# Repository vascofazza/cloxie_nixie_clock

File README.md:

# Cloxie

Schematics and code for Cloxie: my Nixie Tube Clock.

The circuit and custom PCB are designed around the popular IN-14 Nixie tubes.

You can find the schematics here: https://github.com/vascofazza/cloxie_nixie_clock/blob/main/nixie_board/schematics.pdf

Watch the clock in action: https://www.youtube.com/watch?v=ZD35oEGX9IY

## Features

- NTP time sync over Wi-Fi
- The tubes are dimmable via PWM
- 6 RGB leds under the tubes with configurable patterns
- Automatic brightness control with a photoresistor
- Configurable via an onboard web server (reachable on the local network at: http://cloxie.local)
- Configurable via a dedicated Android App (available here: https://github.com/vascofazza/Cloxie-connect)
- Optional temperature sensor
- Alarm/Timer/StopWatch functionalities

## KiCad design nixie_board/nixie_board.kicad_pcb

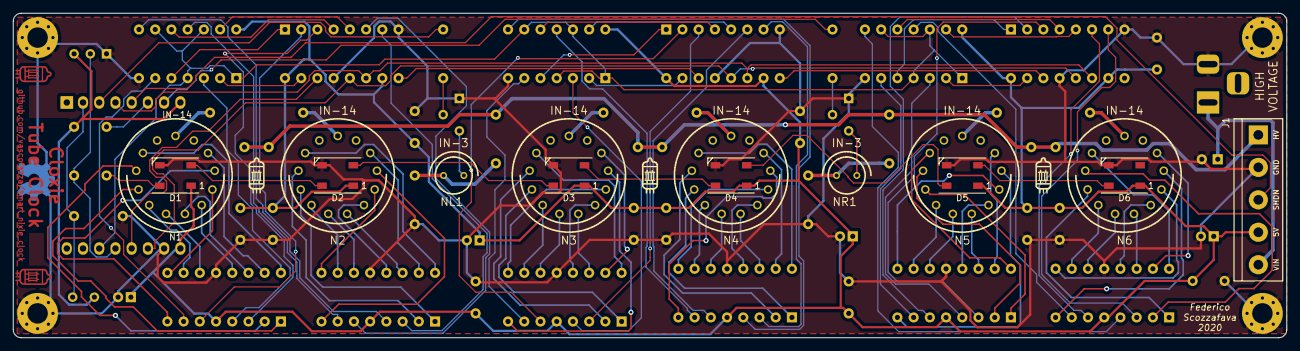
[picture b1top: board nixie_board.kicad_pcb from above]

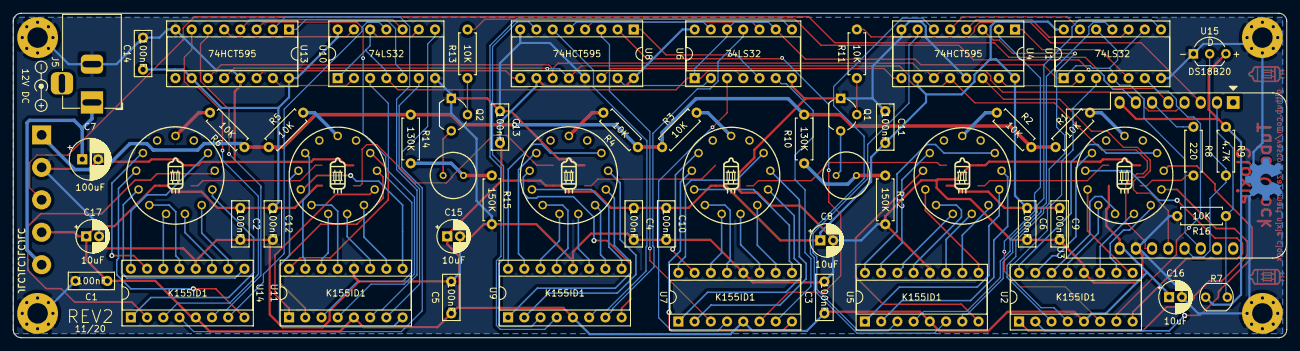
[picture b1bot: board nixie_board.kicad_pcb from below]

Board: 2 copper layers, 199.4 x 50.8 mm, 85 parts (59 on the bottom side), 131 nets.

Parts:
C1, C2, C3, C4, C5, C6, C9, C10, C11, C12, C13, C14: 100nF; C_Disc_D7.0mm_W2.5mm_P5.00mm
C7: 100uF; CP_Radial_D6.3mm_P2.50mm
C8, C15, C16, C17: 10uF; CP_Radial_D5.0mm_P2.00mm
D1, D2, D3, D4, D5, D6: WS2812B; LED_WS2812B_PLCC4_5.0x5.0mm_P3.2mm
H1, H2, H3, H4: MountingHole_Pad; MountingHole_3.2mm_M3_Pad_Via
J1: POWER; TerminalBlock_bornier-5_P5.08mm
J5: Barrel_Jack_Switch; BarrelJack_Horizontal
N1, N2, N3, N4, N5, N6: IN-14; nixies-us-IN-14
NL1: IN-3; nixies-us-IN-3
NR1: IN-3; nixies-us-IN-3
Q1, Q2: MPSA42; TO-92_Wide
R1, R2, R3, R4, R5, R6, R11, R13, R16: 10K; R_Axial_DIN0207_L6.3mm_D2.5mm_P7.62mm_Horizontal
R7: R_PHOTO; R_LDR_5.1x4.3mm_P3.4mm_Vertical
R8: 220; R_Axial_DIN0207_L6.3mm_D2.5mm_P7.62mm_Horizontal
R9: 4.7K; R_Axial_DIN0207_L6.3mm_D2.5mm_P7.62mm_Horizontal
R10, R14: 130K; R_Axial_DIN0207_L6.3mm_D2.5mm_P7.62mm_Horizontal
R12, R15: 150K; R_Axial_DIN0207_L6.3mm_D2.5mm_P7.62mm_Horizontal
S1: Symbol_Barrel_Polarity
S2, S2b: OSHW-Symbol_6.7x6mm_Copper
S4, S5: LOGO; tube
S6, S7, S8, S9, S10, S11, S12, S13, S15, S16, S17: LOGO; tube_silk
U1, U6, U10: 74LS32; DIP-14_W7.62mm_Socket
U2, U5, U7, U9, U11, U14: K155ID1; DIP-16_W7.62mm_Socket
U3: WeMos_D1_mini; WEMOS_D1_mini_light
U4, U8, U13: 74HCT595; DIP-16_W7.62mm_Socket
U15: DS18B20; TO-92_Inline_Wide

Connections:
/3.3V: R7.1, R9.1, U3.8, U15.3
/5V: C1.1, C2.1, C3.1, C4.1, C5.1, C6.1, C8.1, C9.1, C10.1, C11.1, C12.1, C13.1, C14.1, C15.1, C16.1, C17.1, D1.1, D2.1, D3.1, D4.1, D5.1, D6.1, J1.4, U1.14, U2.5, U3.9, U4.10, U4.16, U5.5, U6.14, U7.5, U8.10, U8.16, U9.5, U10.14, U11.5, U13.10, U13.16, U14.5
/170V: J1.1, R1.1, R2.1, R3.1, R4.1, R5.1, R6.1, R10.1, R14.1
/LEFT_DOT: R11.2, U3.3
/RCLK: U3.11, U4.12, U8.12, U13.12
/RGB: R8.1, U3.6
/RIGHT_DOT: R13.2, U3.7
/SER: U3.12, U4.14
/SHUTDOWN: J1.3, U3.5
/SRCLK: U3.4, U4.11, U8.11, U13.11
/STROBE: U1.1, U1.4, U1.9, U1.12, U3.14, U6.1, U6.4, U6.9, U6.12, U10.1, U10.4, U10.9, U10.12
GND: C1.2, C2.2, C3.2, C4.2, C5.2, C6.2, C7.2, C8.2, C9.2, C10.2, C11.2, C12.2, C13.2, C14.2, C15.2, C16.2, C17.2, D1.3, D2.3, D3.3, D4.3, D5.3, D6.3, H1.1, H2.1, H3.1, H4.1, J1.2, J5.2, Q1.1, Q2.1, R12.2, R15.2, R16.2, U1.7, U2.12, U3.10, U4.8, U4.13, U5.12, U6.7, U7.12, U8.8, U8.13, U9.12, U10.7, U11.12, U13.8, U13.13, U14.12, U15.1
unnamed: C7.1, J1.5, J5.1
unnamed: D1.2, D2.4
unnamed: D1.4, R8.2
unnamed: D2.2, D3.4
unnamed: D3.2, D4.4
unnamed: D4.2, D5.4
unnamed: D5.2, D6.4
unnamed: N1.0, U2.16
unnamed: N1.1, U2.15
unnamed: N1.2, U2.8
unnamed: N1.3, U2.9
unnamed: N1.4, U2.13
unnamed: N1.5, U2.14
unnamed: N1.6, U2.11
unnamed: N1.7, U2.10
unnamed: N1.8, U2.1
unnamed: N1.9, U2.2
unnamed: N1.A, R1.2
unnamed: N2.0, U5.16
unnamed: N2.1, U5.15
unnamed: N2.2, U5.8
unnamed: N2.3, U5.9
unnamed: N2.4, U5.13
unnamed: N2.5, U5.14
unnamed: N2.6, U5.11
unnamed: N2.7, U5.10
unnamed: N2.8, U5.1
unnamed: N2.9, U5.2
unnamed: N2.A, R2.2
unnamed: N3.0, U7.16
unnamed: N3.1, U7.15
unnamed: N3.2, U7.8
unnamed: N3.3, U7.9
unnamed: N3.4, U7.13
unnamed: N3.5, U7.14
unnamed: N3.6, U7.11
unnamed: N3.7, U7.10
unnamed: N3.8, U7.1
unnamed: N3.9, U7.2
unnamed: N3.A, R3.2
unnamed: N4.0, U9.16
unnamed: N4.1, U9.15
unnamed: N4.2, U9.8
unnamed: N4.3, U9.9
unnamed: N4.4, U9.13
unnamed: N4.5, U9.14
unnamed: N4.6, U9.11
unnamed: N4.7, U9.10
unnamed: N4.8, U9.1
unnamed: N4.9, U9.2
unnamed: N4.A, R4.2
unnamed: N5.0, U11.16
unnamed: N5.1, U11.15
unnamed: N5.2, U11.8
unnamed: N5.3, U11.9
unnamed: N5.4, U11.13
unnamed: N5.5, U11.14
unnamed: N5.6, U11.11
unnamed: N5.7, U11.10
unnamed: N5.8, U11.1
unnamed: N5.9, U11.2
unnamed: N5.A, R5.2
unnamed: N6.0, U14.16
unnamed: N6.1, U14.15
unnamed: N6.2, U14.8
unnamed: N6.3, U14.9
unnamed: N6.4, U14.13
unnamed: N6.5, U14.14
unnamed: N6.6, U14.11
unnamed: N6.7, U14.10
unnamed: N6.8, U14.1
unnamed: N6.9, U14.2
unnamed: N6.A, R6.2
unnamed: NL1.A, R10.2, R12.1
unnamed: NL1.K, Q1.3
unnamed: NR1.A, R14.2, R15.1
unnamed: NR1.K, Q2.3
unnamed: Q1.2, R11.1
unnamed: Q2.2, R13.1
unnamed: R9.2, U3.13, U15.2
unnamed: R7.2, R16.1, U3.2
unnamed: U1.2, U4.15
unnamed: U1.3, U2.4
unnamed: U1.5, U4.1
unnamed: U1.6, U2.7
unnamed: U1.8, U5.4
unnamed: U1.10, U4.4
unnamed: U1.11, U5.7
unnamed: U1.13, U4.5
unnamed: U2.3, U4.3
unnamed: U2.6, U4.2
unnamed: U4.6, U5.6
unnamed: U4.7, U5.3
unnamed: U4.9, U8.14
unnamed: U6.2, U8.15
unnamed: U6.3, U7.4
unnamed: U6.5, U8.1
unnamed: U6.6, U7.7
unnamed: U6.8, U9.4
unnamed: U6.10, U8.4
unnamed: U6.11, U9.7
unnamed: U6.13, U8.5
unnamed: U7.3, U8.3
unnamed: U7.6, U8.2
unnamed: U8.6, U9.6
unnamed: U8.7, U9.3
unnamed: U10.2, U13.15
unnamed: U10.3, U11.4
unnamed: U10.5, U13.1
unnamed: U10.6, U11.7
unnamed: U10.8, U14.4
unnamed: U10.10, U13.4
unnamed: U10.11, U14.7
unnamed: U10.13, U13.5
unnamed: U11.3, U13.3
unnamed: U11.6, U13.2
unnamed: U13.6, U14.6
unnamed: U13.7, U14.3
unnamed: U8.9, U13.14

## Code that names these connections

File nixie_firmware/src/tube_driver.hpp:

#ifndef TUBE_DRIVER_HPP
#define TUBE_DRIVER_HPP

#include <elapsedMillis.h>
#include <EveryTimer.h>
#include "configuration.hpp"
#include "sensors.hpp"
#include "utils.hpp"
#include <Ticker.h>

#define LEFT_DOT D0
#define RIGHT_DOT D8
#define STROBE D1
#define SHF_LATCH D4
#define SHF_CLOCK D5
#define SHF_DATA D3
#define SHUTDOWN_PIN D6

class TubeDriver
{
private:
    int16_t brightness;
    int16_t l_dot_brightness;
    int16_t r_dot_brightness;
    bool status;
    bool int_status;
    Ticker tube_ticker;
    EveryTimer cathode_poisoning_cycle;
    SensorDriver *sensor_driver;
    void adjust_brightness();
    void set_tube_brightness(int16_t, int16_t, int16_t);

public:
    TubeDriver(SensorDriver *);

    void run_test();

    void loop();

    void set_tubes(int8_t, int8_t, int8_t, int8_t, int8_t, int8_t);

    void set_brightness(int16_t);

    void set_dots_brightness(int16_t, int16_t);

    void display_time_and_date(int8_t, int8_t, int8_t, bool);

    void display_temperature(float);

    void shutdown();

    void turn_off(bool);

    void turn_on(bool);

    bool get_status();

    void cathode_poisoning_prevention(unsigned long);
};

#endif

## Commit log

2020-10-04 mac os gitignore
2020-10-04 rev 0.1
2020-10-06 update gitignore for kikad
2020-10-06 schematic revision + first PCB
2020-10-06 rev 0.2
2020-10-06 clearence review
2020-10-08 first commit for code
2020-10-08 board review 3
2020-10-12 final board review
2020-10-12 test sketch
2020-10-12 gitignore credentials
2020-10-12 test sketch update accounting new features
2020-10-12 PCB version 2
2020-10-14 huge step forward
2020-10-14 PROGMEM + typo fix
2020-10-15 name update
2020-10-15 handling more parameters
2020-10-17 pcb measurements
2020-11-01 massive update + migration to platformIO + v2 HW preparation
2020-11-01 refactoring + timer implementation
2020-11-02 timer fix
2020-11-02 update cycle timeouts
2020-11-02 cycle fix
2020-11-02 default values
2020-11-02 dependency update
2020-11-03 update CI
2020-11-03 GitHub OTA firmware update
2020-11-03 shrinking libraries and moving constants to flash memory
2020-11-03 v0.0.1
2020-11-04 GitHub FOTA fix
2020-11-04 fix workflow
2020-11-04 memory optimization
2020-11-05 led patterns, led modes, dynamic shutdown, bugfixes
2020-11-06 v0.0.3
2020-11-06 parameter callback
2020-11-06 pcb REV1
2020-11-06 wifi connection and reset update
2020-11-06 debug flag
2020-11-07 small fix
2020-11-11 bugfixes
2020-11-11 board rev2
2020-11-11 fade out and fade in
2020-11-11 push version 0.0.4
2020-11-13 adding async support library for WiFiManager
2020-11-13 strings update
2020-11-14 refactoring
2020-11-15 clock update fix
2020-11-15 led and sensors async update
2020-11-15 disable debug flag
2020-11-15 typing refactoring
2020-11-15 fade function improvement
2020-11-15 v0.0.5
2020-11-16 shutdown high impedance fix
2020-11-16 rev2 board fix
2020-11-22 brightness fix
2020-12-07 rev2 board
2020-12-07 pdf schematics
2020-12-08 restful methods
2020-12-08 v1.0.0
2020-12-08 device status request
2020-12-13 temp/date parameters + optimizations
2020-12-13 merging OTA webserver + refactoring
2020-12-13 freeing resource fix
2020-12-13 1.1.0
2020-12-13 1.1.1
2020-12-13 fixup
2020-12-23 remote timer control
2020-12-24 1.1.3
2020-12-24 stopwatch feature + clock_cycle parameter
2020-12-29 remove depoisoning interval
2020-12-29 1.1.3.1
2020-12-30 bugfix
2021-01-01 1.1.3.3
2021-01-01 timezone dependency fix
2021-01-02 improved timezone handling
2021-01-02 css improvements
2021-01-02 1.2.0 release
2021-01-02 fix bad timezone
2021-01-02 flash string helper fix
2021-01-04 wifi reconnect stability improvement
2021-01-04 favicon
2021-01-04 update menu
2021-01-04 new led patterns
2021-01-04 automatic calibration routine
2021-01-04 calibration fix
2021-01-06 reconnection issue fix
2021-01-06 1.4.1
2021-01-07 led patterns bugfixes
2021-01-07 timer patterns
2021-02-04 dependencies update
2021-02-09 new parameters
2021-02-09 baud rate
2021-02-09 memory usage improvements
2021-02-09 remove sensor pre-feed
2021-02-09 1.4.3
2021-03-03 Fix bug on sleep hours
    The bug causes the clock sleeping at any time when the sleep hour
    set is greater than the wake hour (very common when setting the
    sleep hours at night).
    This fix handles the change at midnight.
2021-03-03 1.4.4
2021-09-14 sensor calls and libraries upgrade
2021-09-14 fixes
2021-09-14 enable OTA
